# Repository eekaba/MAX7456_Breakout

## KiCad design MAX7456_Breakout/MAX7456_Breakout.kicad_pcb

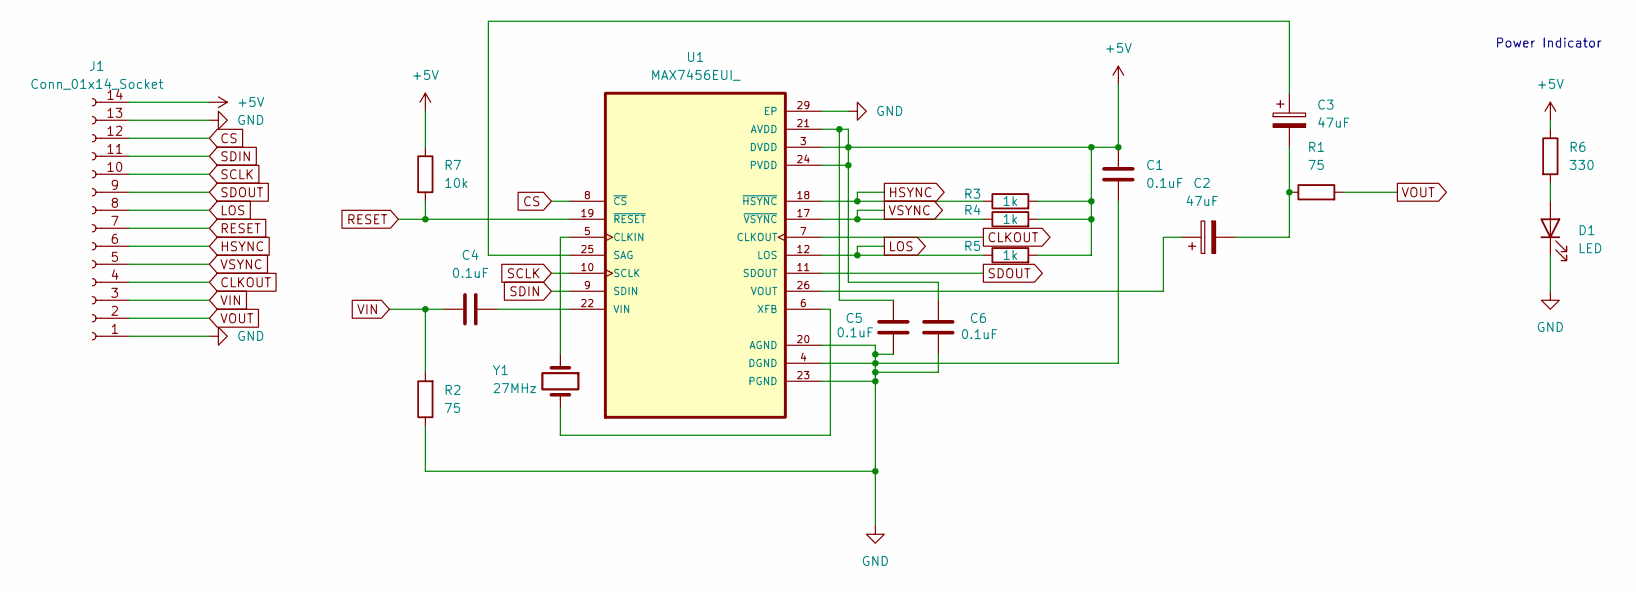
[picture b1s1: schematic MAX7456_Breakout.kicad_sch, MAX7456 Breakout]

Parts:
C1, C4, C5, C6: 0.1uF; C_0402_1005Metric_Pad0.74x0.62mm_HandSolder
C2, C3: 47uF; CAP_293D_B_VIS
D1: LED; LED_0805_2012Metric
J1: Conn_01x14_Socket; PinSocket_1x14_P2.54mm_Vertical
R1, R2: 75; R_0402_1005Metric_Pad0.72x0.64mm_HandSolder
R3, R4, R5: 1k; R_0402_1005Metric_Pad0.72x0.64mm_HandSolder
R6: 330; R_0402_1005Metric_Pad0.72x0.64mm_HandSolder
R7: 10k; R_0402_1005Metric_Pad0.72x0.64mm_HandSolder
U1: MAX7456EUI_; SOP65P637X110-28N
Y1: 27MHz; XTAL_ASV-27.000MHZ-EJ-T

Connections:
+5V: C1.1, C5.1, C6.1, J1.14, R3.2, R4.2, R5.2, R6.1, R7.1, U1.3 (DVDD), U1.21 (AVDD), U1.24 (PVDD)
CLKOUT: J1.4, U1.7 (CLKOUT)
CS: J1.12, U1.8 (~CS)
GND: C1.2, C5.2, C6.2, D1.1 (K), J1.1, J1.13, R2.1, U1.4 (DGND), U1.20 (AGND), U1.23 (PGND), U1.29 (EP)
HSYNC: J1.6, R3.1, U1.18 (~HSYNC)
LOS: J1.8, R5.1, U1.12 (LOS)
unnamed: C2.2, C3.2, R1.1
unnamed: D1.2 (A), R6.2
unnamed: U1.5 (CLKIN), Y1.1
unnamed: C3.1, U1.25 (SAG)
unnamed: C4.2, U1.22 (VIN)
unnamed: C2.1, U1.26 (VOUT)
unnamed: U1.6 (XFB), Y1.2
RESET: J1.7, R7.2, U1.19 (~RESET)
SCLK: J1.10, U1.10 (SCLK)
SDIN: J1.11, U1.9 (SDIN)
SDOUT: J1.9, U1.11 (SDOUT)
VIN: C4.1, J1.3, R2.2
VOUT: J1.2, R1.2
VSYNC: J1.5, R4.1, U1.17 (~VSYNC)

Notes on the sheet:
Power Indicator

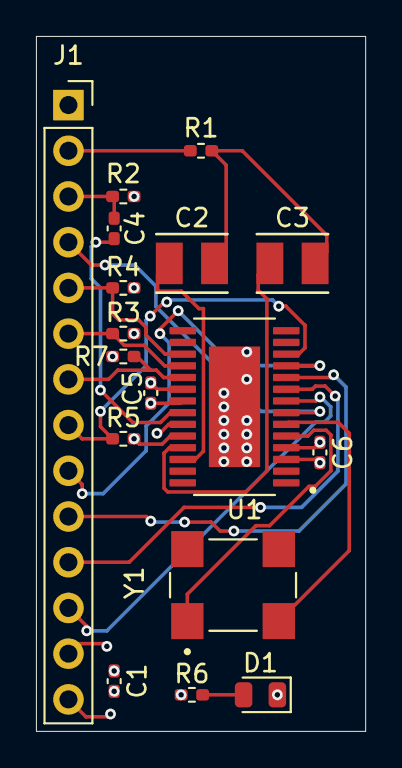
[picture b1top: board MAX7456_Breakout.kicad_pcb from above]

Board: 4 copper layers, 18.3 x 38.6 mm, 17 parts (0 on the bottom side), 20 nets.

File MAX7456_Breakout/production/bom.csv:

Designator,Footprint,Quantity,Value,LCSC Part #
"C1, C4, C5, C6",0402,4,0.1uF,
"C2, C3",CAP_293D_B_VIS,2,47uF,
D1,0805,1,LED,
J1,PinSocket_1x14_P2.54mm_Vertical,1,Conn_01x14_Socket,
"R1, R2",0402,2,75,
"R3, R4, R5",0402,3,1k,
R6,0402,1,330,
U1,SOP65P637X110-28N,1,MAX7456EUI_,
Y1,XTAL_ASV-27.000MHZ-EJ-T,1,27MHz,

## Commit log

2024-08-22 First revision
2024-08-25 Added 10k pullup on reset
